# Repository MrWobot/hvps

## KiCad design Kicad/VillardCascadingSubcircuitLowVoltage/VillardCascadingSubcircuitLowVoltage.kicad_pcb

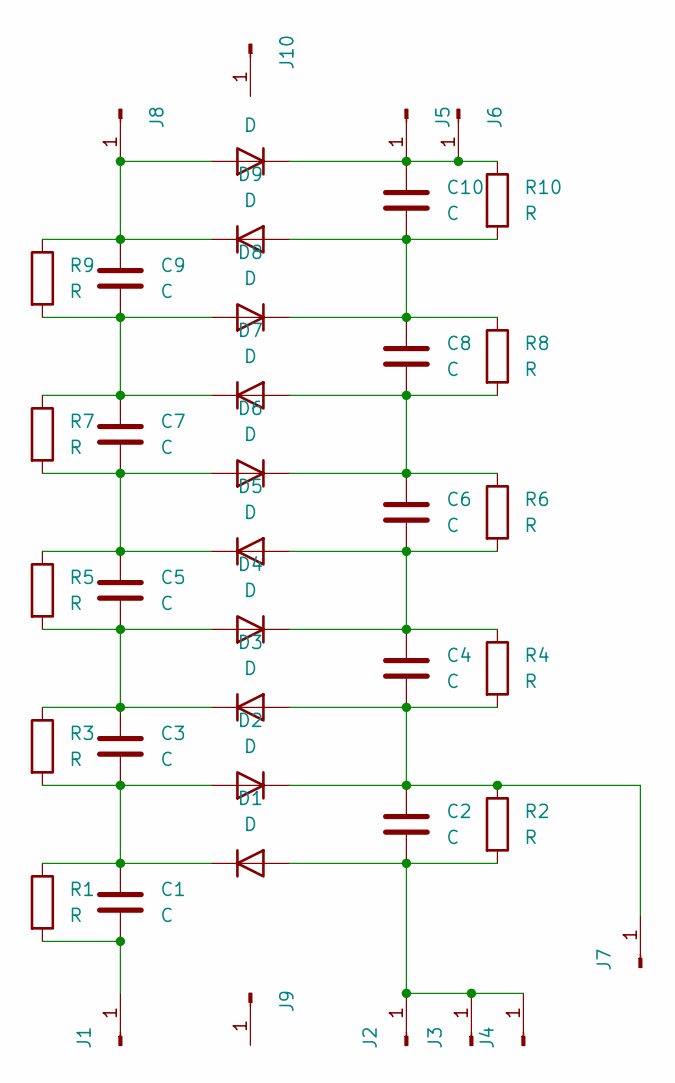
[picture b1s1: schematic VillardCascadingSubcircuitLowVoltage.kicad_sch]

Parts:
C1, C2, C3, C4, C5, C6, C7, C8, C9, C10: C; CBB22_125J630V
D1, D2, D3, D4, D5, D6, D7, D8, D9, D10: D; D_DO-201AD_P15.24mm_Horizontal
J1, J2, J3, J4, J5, J6, J7, J8: Conn_01x01_Pin; VersatilePad
J9, J10: Conn_01x01_Pin; M2.5Hole
R1, R2, R3, R4, R5, R6, R7, R8, R9, R10: R; R_Axial_DIN0309_L9.0mm_D3.2mm_P12.70mm_Horizontal

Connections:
unnamed: C2.2, D1.2 (A), J2.1, J3.1, J4.1, R2.2
unnamed: C1.1, C3.2, D1.1 (K), D2.2 (A), R1.1, R3.2
unnamed: C2.1, C4.2, D2.1 (K), D3.2 (A), J7.1, R2.1, R4.2
unnamed: C3.1, C5.2, D3.1 (K), D4.2 (A), R3.1, R5.2
unnamed: C4.1, C6.2, D4.1 (K), D5.2 (A), R4.1, R6.2
unnamed: C5.1, C7.2, D5.1 (K), D6.2 (A), R5.1, R7.2
unnamed: C6.1, C8.2, D6.1 (K), D7.2 (A), R6.1, R8.2
unnamed: C7.1, C9.2, D7.1 (K), D8.2 (A), R7.1, R9.2
unnamed: C8.1, C10.2, D8.1 (K), D9.2 (A), R8.1, R10.2
unnamed: C9.1, D9.1 (K), D10.2 (A), J8.1, R9.1
unnamed: C10.1, D10.1 (K), J5.1, J6.1, R10.1
unnamed: C1.2, J1.1, R1.2

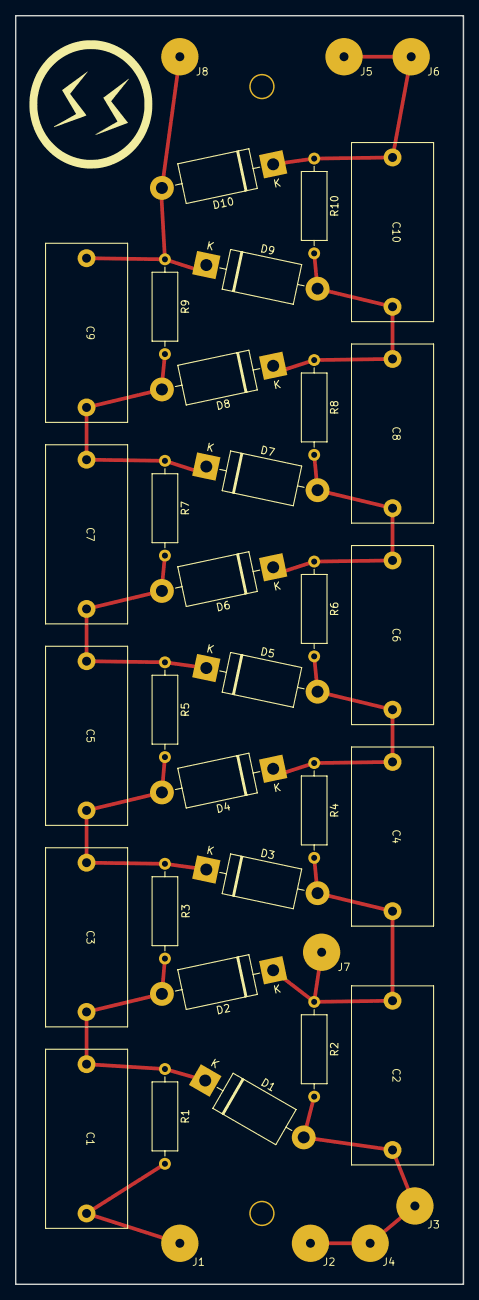
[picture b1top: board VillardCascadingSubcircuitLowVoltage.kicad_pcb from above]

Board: 2 copper layers, 60.0 x 170.0 mm, 40 parts (0 on the bottom side), 12 nets.

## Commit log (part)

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2026-06-12 ignore file.
2026-06-12 new github because lost access.
2026-06-12 C++ shared library for hvps.
2026-06-12 icons and javascript ui
2026-06-12 Full matlab simulation
2026-06-12 PinNumberAsFrequency
    This is used to just confirm all pins function as expected
2026-06-12 more of the c++
2026-06-12 more javascript.
2026-06-12 assembly
2026-06-12 verilog
2026-06-12 more.
2026-06-12 getting there.
2026-06-12 more
2026-06-12 and thats all of it
